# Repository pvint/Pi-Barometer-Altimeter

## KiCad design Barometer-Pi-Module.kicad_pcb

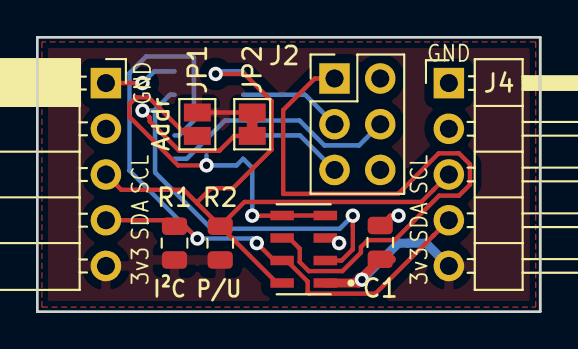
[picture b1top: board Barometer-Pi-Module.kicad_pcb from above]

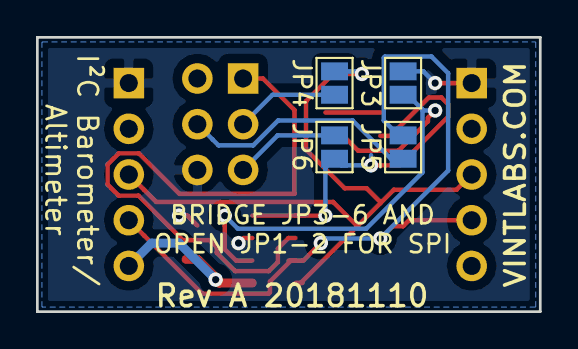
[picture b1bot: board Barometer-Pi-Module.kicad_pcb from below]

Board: 2 copper layers, 27.9 x 15.2 mm, 13 parts (4 on the bottom side), 10 nets.

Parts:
C1: 0.1uF; C_0805_2012Metric
J1: Conn_01x05; PinSocket_1x05_P2.54mm_Horizontal
J2: Conn_02x03_Odd_Even; PinHeader_2x03_P2.54mm_Vertical
J4: Conn_01x05; PinHeader_1x05_P2.54mm_Horizontal
JP1, JP3, JP4, JP5, JP6: SolderJumper_2_Open; SolderJumper-2_P1.3mm_Open_Pad1.0x1.5mm
JP2: Jumper_2_Bridged; SolderJumper-2_P1.3mm_Bridged_Pad1.0x1.5mm
R1, R2: 10k; R_0805_2012Metric
U1: MS560702BA03-50; SON125P300X500X100-8N

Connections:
CSB: JP1.2, JP6.1, U1.4, U1.5
Earth: C1.2, J1.1, J2.6, J4.1, JP3.2, U1.3
PS: JP2.2, JP3.1, U1.2
SCL: J1.3, J4.3, JP4.2, R2.2, U1.8
SDA: J1.4, J4.4, JP5.2, R1.2, U1.7
SPI_CS: J2.5, JP6.2
SPI_MISO: J2.1, U1.6
SPI_MOSI: J2.4, JP5.1
SPI_SCK: J2.3, JP4.1
VDD: C1.1, J1.5, J4.5, JP1.1, JP2.1, R1.1, R2.1, U1.1

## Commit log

2018-11-10 Initial Import
2018-11-11 Tidy silk
2018-11-11 Created gerbers
2018-11-11 Saved status after gerber creation
